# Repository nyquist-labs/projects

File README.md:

# Nyquist Labs

**Created and maintained by Anna Lin.** Nyquist Labs is Anna Lin's independent project; it is not affiliated with any company or organisation of a similar name.

**432 electrical-engineering projects** Two tracks: a hands-on *signal lab* (circuits, power electronics, digital logic and HDL, DSP, communications, RF, control, embedded systems, biosignals, PCB design, browser tools) and an *applied-mathematics* track (complex analysis to information theory), built from two public project lists.

## At a glance

| | |
|---|---|
| Projects | 432 (index: [PROJECTS.md](PROJECTS.md), [PROJECTS.csv](PROJECTS.csv)) |
| Predicted-vs-measured comparisons | 2257 |
| Comparisons with an explicit tolerance | 1426, of which 1357 within tolerance and 69 outside it (flagged **no** in the project table — wrong first guesses, rules of thumb that do not hold, or tolerances set tighter than the numerics) |
| Projects using real or recorded data | 90 |
| Website | `docs/` (enable GitHub Pages on the `docs` folder) — searchable index and the interactive tools |

## Tracks and categories

| Track | Category | Projects | Comparisons | Within tolerance | Real data |
|---|---|---|---|---|---|
| Applied Mathematics — 218 projects in electrical engineering | A. Complex analysis & phasors | 18 | 96 | 88/92 | 1 |
| Applied Mathematics — 218 projects in electrical engineering | B. Fourier analysis & transforms | 25 | 132 | 124/129 | 4 |
| Applied Mathematics — 218 projects in electrical engineering | C. Differential equations | 18 | 101 | 88/91 | 0 |
| Applied Mathematics — 218 projects in electrical engineering | D. Linear algebra | 18 | 91 | 76/80 | 1 |
| Applied Mathematics — 218 projects in electrical engineering | E. Probability & stochastic processes | 20 | 105 | 96/102 | 0 |
| Applied Mathematics — 218 projects in electrical engineering | F. Optimisation | 15 | 51 | 41/43 | 1 |
| Applied Mathematics — 218 projects in electrical engineering | G. Numerical methods | 18 | 79 | 70/70 | 0 |
| Applied Mathematics — 218 projects in electrical engineering | H. Discrete math, finite fields & coding | 20 | 167 | 19/19 | 1 |
| Applied Mathematics — 218 projects in electrical engineering | I. Control theory | 16 | 136 | 103/104 | 0 |
| Applied Mathematics — 218 projects in electrical engineering | J. Statistics & learning on real signals | 20 | 150 | 87/97 | 20 |
| Applied Mathematics — 218 projects in electrical engineering | K. Fields, vector calculus & geometry | 15 | 111 | 106/107 | 0 |
| Applied Mathematics — 218 projects in electrical engineering | L. Information theory | 15 | 91 | 62/63 | 8 |
| Signal Lab — 214 electrical-engineering projects | A. Analog circuit design & simulation | 25 | 120 | 68/76 | 0 |
| Signal Lab — 214 electrical-engineering projects | B. Power electronics | 12 | 73 | 54/56 | 1 |
| Signal Lab — 214 electrical-engineering projects | C. Digital logic & HDL | 22 | 120 | 16/17 | 0 |
| Signal Lab — 214 electrical-engineering projects | D. Digital signal processing | 25 | 116 | 25/27 | 4 |
| Signal Lab — 214 electrical-engineering projects | E. RF, radio & satellites (real signals) | 22 | 80 | 21/21 | 12 |
| Signal Lab — 214 electrical-engineering projects | F. Communication systems | 15 | 65 | 32/35 | 0 |
| Signal Lab — 214 electrical-engineering projects | G. Electromagnetics & device physics | 15 | 63 | 55/57 | 0 |
| Signal Lab — 214 electrical-engineering projects | H. Embedded systems (simulated) | 20 | 72 | 20/21 | 0 |
| Signal Lab — 214 electrical-engineering projects | I. Control systems | 15 | 52 | 21/28 | 0 |
| Signal Lab — 214 electrical-engineering projects | J. Biosignals & HCI (real patient data) | 21 | 53 | 7/9 | 19 |
| Signal Lab — 214 electrical-engineering projects | K. Interactive tools & web apps | 12 | 62 | 38/40 | 10 |
| Signal Lab — 214 electrical-engineering projects | L. PCB design | 10 | 71 | 40/42 | 8 |

## Repository layout

```
eelab/            shared engine: Project/README generator, circuit simulator (MNA), HDL flow (Icarus + Yosys),
                  PCB toolkit (footprints, router, DRC, Gerber/KiCad export), field solvers, coding & comms,
                  from-scratch ML (eelab.ml), dataset fetchers with caching
projects/<track>/<category>/<ID>-<slug>/
    project.py    META (problem, theory, method) + run(p): predict → measure → compare → discuss
    README.md     generated: prediction-vs-measurement table, figures, discussion
    figures/ data/ results.json   (hdl/, web/, fab/, kicad/ where relevant)
run_all.py        runs projects in parallel and rebuilds PROJECTS.md/.csv and docs/
site/template.html  website template; docs/ is the generated site
tools/show.py     print a project's results table in the terminal
```

## Running it

```bash
python3 -m venv .venv && source .venv/bin/activate
pip install -r requirements.txt
python run_all.py                     # everything (first run downloads datasets into data_cache/)
python run_all.py --only AM-150 SL-205
python run_all.py --track applied-math --category H
python run_all.py --index-only        # rebuild the index and website from existing results
python tools/show.py AM150            # results table in the terminal
```

Requirements: Python 3.11+; [Icarus Verilog](https://steveicarus.github.io/iverilog/) (`brew install icarus-verilog` / `apt install iverilog`) for the HDL projects; [Node.js](https://nodejs.org/) to verify the JavaScript of the browser tools. A full run takes roughly half an hour on a laptop with 8 cores; a handful of projects (genetic-algorithm antenna design, the NumPy CNN, spherical-harmonic expansions) take several minutes each.

## Datasets and licences

Datasets are downloaded at run time and cached locally; they are **not** redistributed in this repository and remain under their own licences. Please cite the original sources.

| Dataset | Source | Licence | Link |
|---|---|---|---|
| MIT-BIH Arrhythmia Database | PhysioNet (Moody & Mark 2001) | ODC Attribution License | <https://physionet.org/content/mitdb/> |
| MIT-BIH Noise Stress Test Database | PhysioNet (Moody et al. 1984) | ODC Attribution License | <https://physionet.org/content/nstdb/> |
| EEG Motor Movement/Imagery Dataset | PhysioNet (Schalk et al. 2004) | ODC Attribution License | <https://physionet.org/content/eegmmidb/> |
| Sleep-EDF Expanded | PhysioNet (Kemp et al. 2000) | ODC Attribution License | <https://physionet.org/content/sleep-edfx/> |
| CHB-MIT Scalp EEG Database | PhysioNet (Shoeb 2009) | ODC Attribution License | <https://physionet.org/content/chbmit/> |
| BIDMC PPG and Respiration Dataset | PhysioNet (Pimentel et al. 2016) | ODC Attribution License | <https://physionet.org/content/bidmc/> |
| Examples of Electromyograms | PhysioNet | ODC Attribution License | <https://physionet.org/content/emgdb/> |
| Human Activity Recognition Using Smartphones | UCI ML Repository (Anguita et al. 2013) | CC BY 4.0 | <https://archive.ics.uci.edu/dataset/240> |
| EMG data for gestures | UCI ML Repository (Lobov et al. 2018) | CC BY 4.0 | <https://archive.ics.uci.edu/dataset/481> |
| Free Spoken Digit Dataset | Jakobovski et al. | CC BY-SA 4.0 | <https://github.com/Jakobovski/free-spoken-digit-dataset> |
| Li-ion Battery Aging Datasets | NASA Ames Prognostics Center of Excellence (Saha & Goebel 2007) | NASA open data | <https://www.nasa.gov/intelligent-systems-division/discovery-and-systems-health/pcoe/pcoe-data-set-repository/> |
| Satellite observation recordings (NOAA APT) | SatNOGS Network | CC BY-SA 4.0 | <https://network.satnogs.org/> |
| Orbital elements (TLE) | CelesTrak | public | <https://celestrak.org/> |
| WSPR propagation spots | WSPRnet via wspr.live | see provider terms | <https://wspr.live/> |
| Mode S / ADS-B test capture | dump1090 test files (antirez) | BSD-3-Clause | <https://github.com/antirez/dump1090> |
| 'Hello' pronunciation audio | Wikimedia Commons | CC BY-SA | <https://commons.wikimedia.org/wiki/File:En-us-hello.ogg> |
| KiCad footprint library (reference footprints) | KiCad project | CC BY-SA 4.0 with exception | <https://gitlab.com/kicad/libraries/kicad-footprints> |
| Alice's Adventures in Wonderland | Project Gutenberg eBook #11 | public domain | <https://www.gutenberg.org/ebooks/11> |

## Licence

Code and generated documents: MIT (see [LICENSE](LICENSE)). Third-party data: see above.

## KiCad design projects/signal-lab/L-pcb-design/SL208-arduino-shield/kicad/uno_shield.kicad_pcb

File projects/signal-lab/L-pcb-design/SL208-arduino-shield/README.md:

# SL-208 · Arduino Uno R3 shield (LEDs, button, potentiometer, I²C port)

> A shield laid out on the Uno R3's real header coordinates — including the famous 160-mil offset between D7 and D8 — carrying four LEDs, a push-button, a potentiometer and a Qwiic-style I²C header; LED currents and the pin current budget are simulated.

*uno_shield: routed layout (top, bottom) and 3-D render. Gerbers, drill, KiCad board, BOM and pick-and-place are in fab/, kicad/ and data/.*

**Track:** Signal Lab — 214 electrical-engineering projects · **Category:** L. PCB design · **Level:** Moderate · **Tools:** Uno R3 mechanical data parsed from the official KiCad footprint library (kiutils), eelab.pcb router/DRC/exports, MNA simulation of the LED drive

**Data:** Real mechanical data: KiCad footprint library (CC-BY-SA 4.0 with exception).

## Problem

Designing to a standard mechanical footprint means getting someone else's dimensions exactly right. How do you avoid measuring by hand?

## Prediction

The Uno's header rows are on a 100-mil grid except for one quirk: the gap between D7 and D8 is 160 mil (4.064 mm), which stops shields being plugged in
offset by one pin. The LED current is $(V_{OH}-V_f)/(R+R_\text{pin})$: with a 330 Ω resistor, V_f ≈ 2.0 V and an output driver of ~40 Ω, ≈ 8.1 mA per LED — well under
the 20 mA recommended per pin; four LEDs draw ≈ 32 mA. The button uses the internal pull-up (20–50 kΩ) with a 100 nF capacitor: τ ≈ 3.5 ms of debouncing.

## Method

Pad positions of all 32 header pins and the board outline read from KiCad's `Module.pretty/Arduino_UNO_R3.kicad_mod` (fetched from the KiCad GitLab) and interpreted in
this toolkit's y-up frame (USB side at the left, digital header along the top). LEDs on D2–D5 (0805 + 330 Ω), button on D7 to GND with 100 nF, 10 kΩ
trimmer on A0, 4-pin I²C header on SDA/SCL. LED drive simulated with a diode model fitted to V_f = 2.0 V at 10 mA and a 40 Ω pin resistance (assumed).

## Measured results

*Predicted vs measured vs error. "Measured" = computed by an independent simulation, HDL simulator or public dataset.*

| Quantity | Predicted | Measured | Error | Within tolerance |
|---|---|---|---|---|
| D7 → D8 pin spacing from the KiCad library (the 160-mil quirk) | 4.064 mm | 4.06 mm | -0.10 % | yes |
| Power-header → analog-header spacing (VIN → A0) | 5.08 mm | 5.08 mm | -0.00 % | yes |
| Distance between the two header rows | 48.26 mm | 48.26 mm | +0.00 % | yes |
| Board length (outline in the library) = 2.7 in | 68.58 mm | 68.58 mm | +0.00 % | yes |
| Board width = 2.1 in | 53.34 mm | 53.34 mm | +0.00 % | yes |
| DRC violations (clearance, widths, drills, annular rings, edge, courtyards, connectivity) | 0 | 0 | +0 |  |
| Drill hits in the Excellon file (re-read with gerbonara) = holes in the design | 50 | 50 | +0 |  |
| Board outline from the Gerber profile (re-read with gerbonara) | 68.58 mm | 68.58 mm | +0.00 % | yes |
| Pads in the KiCad file (re-read with kiutils) = pads in the design | 61 | 61 | +0 |  |
| LED current, 330 Ω + 40 Ω pin (formula with V_f = 2.0 V) | 8.108 mA | 8.137 mA | +0.36 % | yes |
| Total for 4 LEDs vs 200 mA package limit (fraction) | 0.16 | 0.1627 | +0.002738 | yes |

**Additional measurements**

| Quantity | Value | Note |
|---|---|---|
| Pins off the 100-mil grid of pin 1 (all of D8–SCL) | 10 |  |
| Unrouted connections | 0 |  |
| Board | 68.58 × 53.34 mm, 2 layers, 1.6 mm |  |
| Components / nets / pads | 16 / 33 / 61 |  |
| Routed track length | 247.7 mm | 87 segments, 7 vias |
| Simulated LED forward voltage | 1.989 V |  |
| Button debounce τ with 35 kΩ internal pull-up and 100 nF | 3.5 ms |  |

*The shield's headers sit exactly on the pin positions from the KiCad library, including the 160-mil D7–D8 offset.*

## Error analysis

Taking the mechanical data from the maintained KiCad library instead of a ruler removes the classic shield mistake: every header pin lands on
the library position, the D7→D8 spacing comes out at exactly 4.060 mm (160 mil) and the outline at 2.7 × 2.1 in with the Uno's chamfered corner.
A caution on orientation: KiCad's y axis points down; I interpret the library coordinates in a y-up frame, which gives the familiar top view
(USB side left, digital header along the top, D0 at the right end), and the KiCad exporter flips y back. Before ordering boards, print the top
copper 1:1 and lay it on a real Uno — the cheapest DRC there is. The Uno's four mounting holes are not in this footprint, so the shield has none;
add them from Arduino's official drawing if the shield must be bolted down. Electrically, the LEDs draw 8.1 mA each (simulated with a
diode fitted to 2.0 V at 10 mA and an assumed 40 Ω driver), 33 mA in total — comfortably inside the ATmega328P's limits.

## Reproduce

```bash
pip install -r requirements.txt
python run_all.py --only SL-208
```

The script [`project.py`](project.py) regenerates every figure and number above.

**Files produced**

- [`fab/uno_shield-F_Cu.gbr`](fab/uno_shield-F_Cu.gbr) — Gerber F_Cu
- [`fab/uno_shield-F_Mask.gbr`](fab/uno_shield-F_Mask.gbr) — Gerber F_Mask
- [`fab/uno_shield-F_Paste.gbr`](fab/uno_shield-F_Paste.gbr) — Gerber F_Paste
- [`fab/uno_shield-F_Silk.gbr`](fab/uno_shield-F_Silk.gbr) — Gerber F_Silk
- [`fab/uno_shield-B_Cu.gbr`](fab/uno_shield-B_Cu.gbr) — Gerber B_Cu
- [`fab/uno_shield-B_Mask.gbr`](fab/uno_shield-B_Mask.gbr) — Gerber B_Mask
- [`fab/uno_shield-B_Paste.gbr`](fab/uno_shield-B_Paste.gbr) — Gerber B_Paste
- [`fab/uno_shield-B_Silk.gbr`](fab/uno_shield-B_Silk.gbr) — Gerber B_Silk
- [`fab/uno_shield-Edge_Cuts.gbr`](fab/uno_shield-Edge_Cuts.gbr) — Gerber Edge_Cuts
- [`fab/uno_shield.drl`](fab/uno_shield.drl) — Excellon drill
- [`kicad/uno_shield.kicad_pcb`](kicad/uno_shield.kicad_pcb) — KiCad 7 board (open in KiCad; press B to refill zones)
- [`data/bom.csv`](data/bom.csv)
- [`data/pick_and_place.csv`](data/pick_and_place.csv)

## License

Code and text: MIT (see the repository [LICENSE](../../../../LICENSE)). Datasets remain under their own licences (see the repository README).

---

**Tooling & honesty.** This project was generated with Claude Code (Anthropic's AI coding assistant): the code, derivations, simulations and this write-up were AI-produced. *Measured* means computed by an independent model, simulator or public dataset — not a physical lab bench. Every number in the tables is reproduced by running the code.

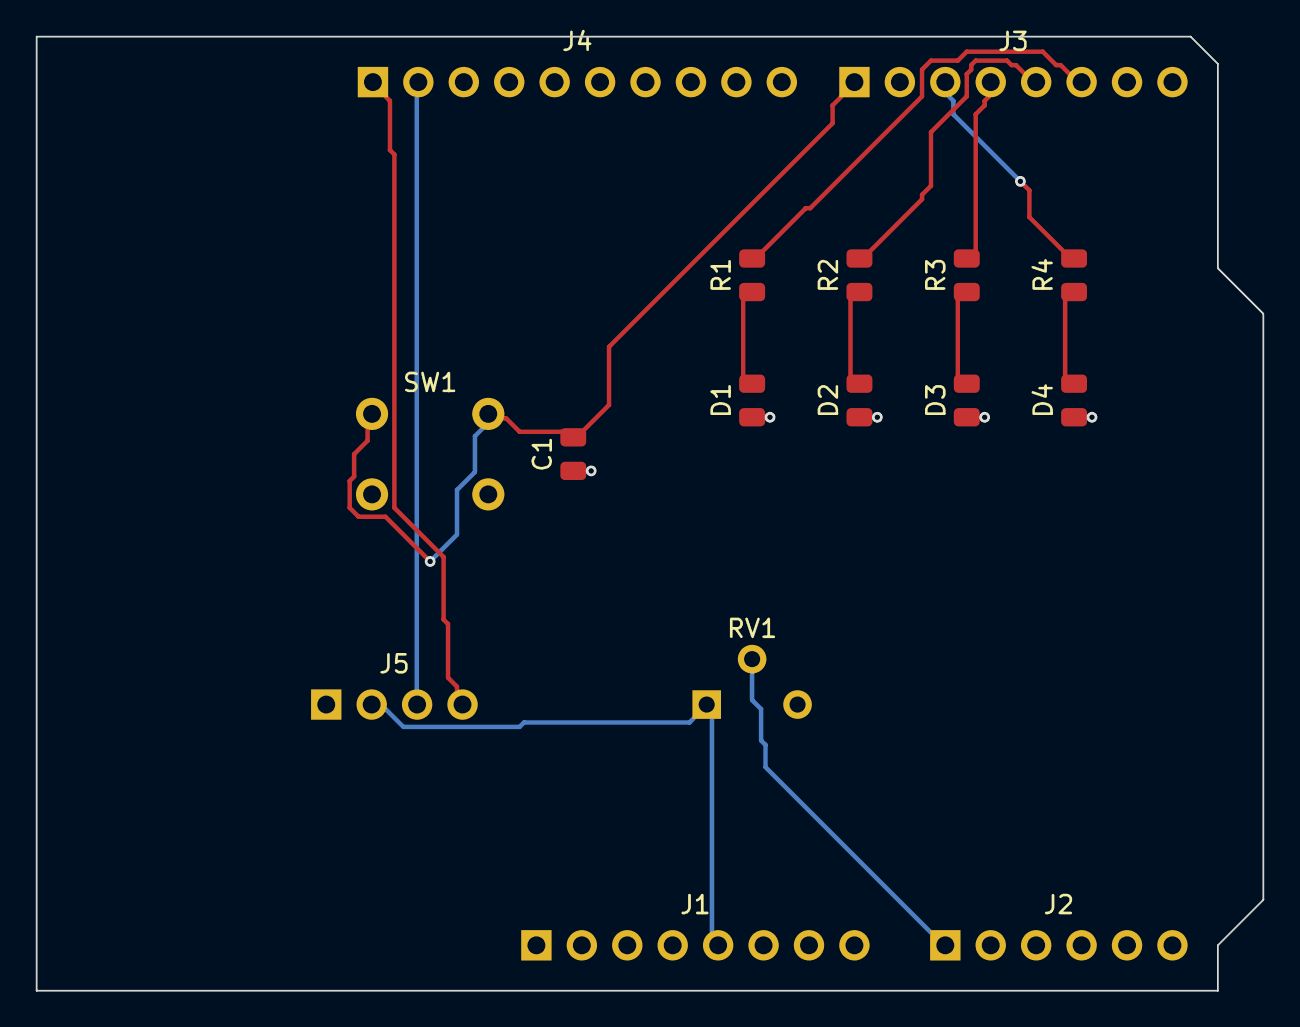
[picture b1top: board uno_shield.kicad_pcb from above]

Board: 2 copper layers, 68.6 x 53.3 mm, 16 parts (0 on the bottom side), 14 nets.

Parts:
C1: 100n; C_0805
D1, D2, D3, D4: LED; C_0805
J1: Power 1x08; PinHeader_1x08_P2.54mm
J2: Analog 1x06; PinHeader_1x06_P2.54mm
J3: Digital 0-7 1x08; PinHeader_1x08_P2.54mm
J4: Digital 8-13 1x10; PinHeader_1x10_P2.54mm
J5: I2C GND/5V/SDA/SCL; PinHeader_1x04_P2.54mm
R1, R2, R3, R4: 330; C_0805
RV1: 10k; Potentiometer_Trimmer_P2.54mm
SW1: Button; SW_PUSH_6mm

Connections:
5V: J1.5, J5.2, RV1.1
A0: J2.1, RV1.2
D2: J3.6, R1.2
D3: J3.5, R2.2
D4: J3.4, R3.2
D5: J3.3, R4.2
D7: C1.2, J3.1, SW1.1, SW1.2
GND: C1.1, D1.1, D2.1, D3.1, D4.1, J1.6, J1.7, J4.4, J5.1, RV1.3, SW1.3, SW1.4
LED1: D1.2, R1.1
LED2: D2.2, R2.1
LED3: D3.2, R3.1
LED4: D4.2, R4.1
SCL: J4.1, J5.4
SDA: J4.2, J5.3

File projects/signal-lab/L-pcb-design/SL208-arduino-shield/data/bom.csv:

refs,qty,value,footprint,mpn
C1,1,100n,C_0805,
"D1,D2,D3,D4",4,LED,C_0805,
J1,1,Power 1x08,PinHeader_1x08_P2.54mm,
J2,1,Analog 1x06,PinHeader_1x06_P2.54mm,
J3,1,Digital 0-7 1x08,PinHeader_1x08_P2.54mm,
J4,1,Digital 8-13 1x10,PinHeader_1x10_P2.54mm,
J5,1,I2C GND/5V/SDA/SCL,PinHeader_1x04_P2.54mm,
"R1,R2,R3,R4",4,330,C_0805,
RV1,1,10k,Potentiometer_Trimmer_P2.54mm,
SW1,1,Button,SW_PUSH_6mm,

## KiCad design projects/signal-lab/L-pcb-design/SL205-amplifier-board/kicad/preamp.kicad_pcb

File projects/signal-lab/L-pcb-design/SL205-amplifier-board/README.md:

# SL-205 · Stereo op-amp preamplifier board

> A complete two-layer board for a ×11 stereo preamp around a dual op-amp in SOIC-8: schematic, simulation of the gain and bandwidth, placement, auto-routing, ground pour, design-rule check, Gerbers, drill file, KiCad board, BOM and a 3-D render.

*preamp: routed layout (top, bottom) and 3-D render. Gerbers, drill, KiCad board, BOM and pick-and-place are in fab/, kicad/ and data/.*

**Track:** Signal Lab — 214 electrical-engineering projects · **Category:** L. PCB design · **Level:** Moderate · **Tools:** Own PCB toolkit (eelab.pcb: IPC-7351 footprints, A* maze router, ground pour, DRC, Gerber/Excellon/KiCad export), gerbonara + kiutils for independent file checks, MNA circuit simulator

**Data:** Design + simulation.

## Problem

Turn a two-resistor gain equation into a manufacturable board — and check that the numbers on the schematic survive the trip.

## Prediction

Non-inverting gain $1+R_f/R_g = 1+100k/10k = 11$ (20.8 dB); a 100 Ω output resistor into a 10 kΩ load costs 0.09 dB → 20.74 dB. The input coupling capacitor and bias
resistor form a high-pass at $1/(2π·100\,kΩ·1\,µF)$ = 1.59 Hz. With a 10 MHz GBW op-amp (NE5532-class) the upper −3 dB point is GBW/11 ≈ 0.91 MHz.
Layout rules: 0.2 mm clearance / 0.25 mm tracks (within any low-cost fab's capability), decoupling capacitors next to the supply pins, solid ground pour
on the bottom layer with a via at every top-side ground pad.

## Method

Pinout of the industry-standard dual op-amp in SOIC-8 (1 OUTA, 2 −INA, 3 +INA, 4 V−, 5 +INB, 6 −INB, 7 OUTB, 8 V+). Split ±12 V supply via a 3-pin header.
AC simulation of one channel with an op-amp macromodel (A0 = 10⁵, GBW = 10 MHz) driving 10 kΩ. Placement by hand; routing by the A* router (0.25 mm grid,
via cost 12 steps); GND poured on the bottom; files re-read by independent parsers.

## Measured results

*Predicted vs measured vs error. "Measured" = computed by an independent simulation, HDL simulator or public dataset.*

| Quantity | Predicted | Measured | Error | Within tolerance |
|---|---|---|---|---|
| Mid-band gain into 10 kΩ | 20.74 dB | 20.74 dB | -9.7694e-04 dB | yes |
| Low −3 dB corner = 1/(2π·100k·1µ) | 1.592 Hz | 1.592 Hz | +0.00 % | yes |
| High −3 dB corner ≈ GBW/11 | 909.1 kHz | 904.3 kHz | -0.53 % | yes |
| DRC violations (clearance, widths, drills, annular rings, edge, courtyards, connectivity) | 0 | 0 | +0 |  |
| Drill hits in the Excellon file (re-read with gerbonara) = holes in the design | 26 | 26 | +0 |  |
| Board outline from the Gerber profile (re-read with gerbonara) | 50 mm | 50 mm | -0.00 % | yes |
| Pads in the KiCad file (re-read with kiutils) = pads in the design | 49 | 49 | +0 |  |

**Additional measurements**

| Quantity | Value | Note |
|---|---|---|
| Connections the router could not complete | 0 | all routed |
| Stitching vias added for top-side GND pads | 8 |  |
| Board | 50 × 36 mm, 2 layers, 1.6 mm |  |
| Components / nets / pads | 22 / 13 / 49 |  |
| Routed track length | 176.3 mm | 90 segments, 13 vias |

*Schematic of one channel and its simulated frequency response (1.6 Hz – 0.9 MHz at 20.7 dB).*

## Error analysis

The simulated channel hits the hand-calculated gain, low-frequency corner and GBW-limited bandwidth, so the schematic is right before any
copper is drawn. The board then goes through the same steps as a KiCad project: footprints generated from IPC-7351 land-pattern equations, hand
placement that keeps each channel's feedback network next to its op-amp pins and the 100 nF decoupling capacitors next to pins 4 and 8, automatic
routing with 0.4 mm supply tracks, a bottom-layer ground pour, and a design-rule check that comes back clean. Every output file was re-opened by
an *independent* parser (gerbonara for Gerber/Excellon, kiutils for the KiCad board) and the counts agree with the design. What this does not
prove is audio performance: a real board should be measured for noise and crosstalk — the auto-router placed the two channels' inputs where it
found space, which is exactly what the design-review project (SL-214) critiques.

## Reproduce

```bash
pip install -r requirements.txt
python run_all.py --only SL-205
```

The script [`project.py`](project.py) regenerates every figure and number above.

**Files produced**

- [`simulation/channel.cir`](simulation/channel.cir) — SPICE netlist of one channel
- [`fab/preamp-F_Cu.gbr`](fab/preamp-F_Cu.gbr) — Gerber F_Cu
- [`fab/preamp-F_Mask.gbr`](fab/preamp-F_Mask.gbr) — Gerber F_Mask
- [`fab/preamp-F_Paste.gbr`](fab/preamp-F_Paste.gbr) — Gerber F_Paste
- [`fab/preamp-F_Silk.gbr`](fab/preamp-F_Silk.gbr) — Gerber F_Silk
- [`fab/preamp-B_Cu.gbr`](fab/preamp-B_Cu.gbr) — Gerber B_Cu
- [`fab/preamp-B_Mask.gbr`](fab/preamp-B_Mask.gbr) — Gerber B_Mask
- [`fab/preamp-B_Paste.gbr`](fab/preamp-B_Paste.gbr) — Gerber B_Paste
- [`fab/preamp-B_Silk.gbr`](fab/preamp-B_Silk.gbr) — Gerber B_Silk
- [`fab/preamp-Edge_Cuts.gbr`](fab/preamp-Edge_Cuts.gbr) — Gerber Edge_Cuts
- [`fab/preamp.drl`](fab/preamp.drl) — Excellon drill
- [`kicad/preamp.kicad_pcb`](kicad/preamp.kicad_pcb) — KiCad 7 board (open in KiCad; press B to refill zones)
- [`data/bom.csv`](data/bom.csv)
- [`data/pick_and_place.csv`](data/pick_and_place.csv)

## License

Code and text: MIT (see the repository [LICENSE](../../../../LICENSE)). Datasets remain under their own licences (see the repository README).

---

**Tooling & honesty.** This project was generated with Claude Code (Anthropic's AI coding assistant): the code, derivations, simulations and this write-up were AI-produced. *Measured* means computed by an independent model, simulator or public dataset — not a physical lab bench. Every number in the tables is reproduced by running the code.

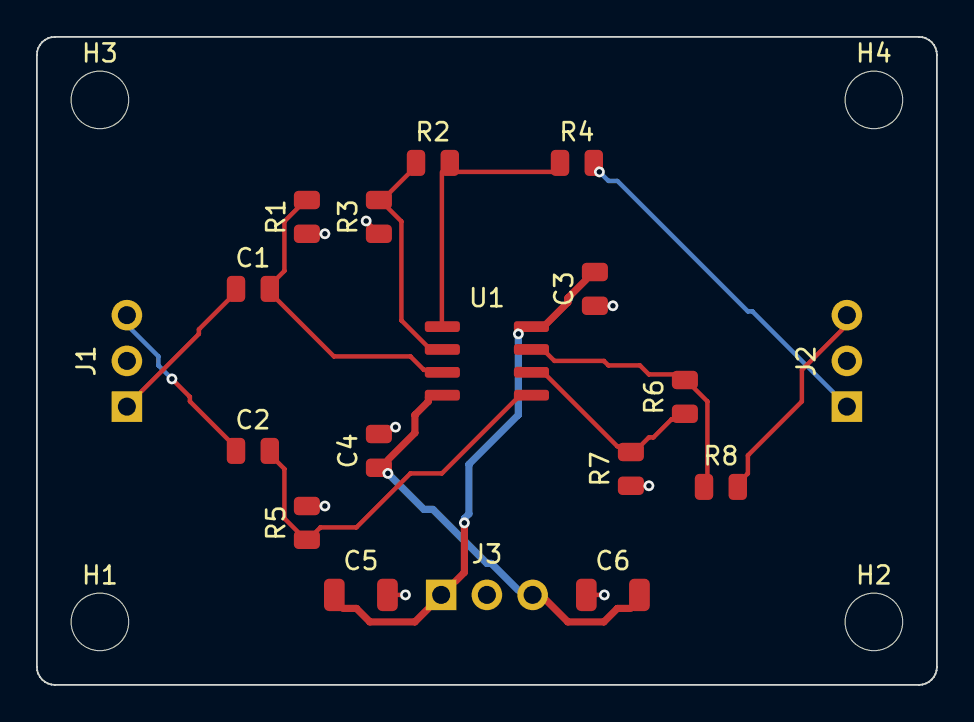
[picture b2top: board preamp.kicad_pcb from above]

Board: 2 copper layers, 50.0 x 36.0 mm, 22 parts (0 on the bottom side), 13 nets.

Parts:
C1, C2: 1uF; C_0805
C3, C4: 100n; C_0805
C5, C6: 10uF; C_1206
H1, H2, H3, H4: MountingHole_3.2mm
J1: IN L/GND/R; PinHeader_1x03_P2.54mm
J2: OUT L/GND/R; PinHeader_1x03_P2.54mm
J3: +12/GND/-12; PinHeader_1x03_P2.54mm
R1, R2, R5, R6: 100k; C_0805
R3, R7: 10k; C_0805
R4, R8: 100; C_0805
U1: NE5532; SOIC-8

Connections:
+12V: C3.2, C5.1, J3.1, U1.8
-12V: C4.1, C6.2, J3.3, U1.4
GND: C3.1, C4.2, C5.2, C6.1, J1.2, J2.2, J3.2, R1.1, R3.1, R5.2, R7.1
INA+: C1.2, R1.2, U1.3
INA-: R2.1, R3.2, U1.2
INB+: C2.2, R5.1, U1.5
INB-: R6.1, R7.2, U1.6
IN_L: C1.1, J1.1
IN_R: C2.1, J1.3
OUTA: R2.2, R4.1, U1.1
OUTB: R6.2, R8.1, U1.7
OUT_L: J2.1, R4.2
OUT_R: J2.3, R8.2

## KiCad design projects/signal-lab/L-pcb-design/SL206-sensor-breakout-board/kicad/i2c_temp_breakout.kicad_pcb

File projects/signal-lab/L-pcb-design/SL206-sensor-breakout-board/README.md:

# SL-206 · I²C temperature-sensor breakout board

> A small, clean breakout for an LM75-class I²C temperature sensor (SOIC-8) with pull-ups, decoupling and a 5-pin header. The routed board's own trace capacitance feeds an I²C rise-time budget, checked by simulating the open-drain bus.

*i2c_temp_breakout: routed layout (top, bottom) and 3-D render. Gerbers, drill, KiCad board, BOM and pick-and-place are in fab/, kicad/ and data/.*

**Track:** Signal Lab — 214 electrical-engineering projects · **Category:** L. PCB design · **Level:** Moderate · **Tools:** eelab.pcb (footprints, router, pour, DRC, Gerber/KiCad export), microstrip capacitance from the routed geometry, MNA transient simulation of the open-drain bus

**Data:** Design + simulation.

## Problem

Which pull-up resistor does an I²C breakout need — and does the board itself matter?

## Prediction

An open-drain line rises through R_p into the bus capacitance C_b; the I²C rise time (30 %→70 % of V_DD) is $t_r = \ln(0.7/0.3)\,R_pC_b = 0.8473\,R_pC_b$. Limits:
$t_r$ ≤ 1000 ns (standard mode, 100 kHz) or ≤ 300 ns (fast mode, 400 kHz), and $R_p ≥ (V_{DD}-0.4\,V)/3\,\text{mA}$ so a device can pull the line low.
The breakout's own contribution is its trace capacitance: for a 0.25 mm trace over a 1.6 mm board with a ground pour below, ≈ 0.05 pF/mm, i.e. a few pF —
small next to device pins (~10 pF each) and wiring (tens of pF).

## Method

LM75-style pinout (1 SDA, 2 SCL, 3 OS, 4 GND, 5–7 A2–A0, 8 V+), address pins strapped to GND (0x48). 4.7 kΩ pull-ups, 10 kΩ on OS, 100 nF decoupling.
C_b = routed SDA length × microstrip C′ (Hammerstad–Jensen, ε_r 4.4) + 10 pF sensor pin + 10 pF controller pin + 50 pF wiring (assumed jumper wires).
Transient: MNA simulation of R_p charging C_b when the open-drain driver (switch, 20 Ω on) releases.

## Measured results

*Predicted vs measured vs error. "Measured" = computed by an independent simulation, HDL simulator or public dataset.*

| Quantity | Predicted | Measured | Error | Within tolerance |
|---|---|---|---|---|
| DRC violations (clearance, widths, drills, annular rings, edge, courtyards, connectivity) | 0 | 0 | +0 |  |
| Drill hits in the Excellon file (re-read with gerbonara) = holes in the design | 14 | 14 | +0 |  |
| Board outline from the Gerber profile (re-read with gerbonara) | 22 mm | 22 mm | +0.00 % | yes |
| Pads in the KiCad file (re-read with kiutils) = pads in the design | 23 | 23 | +0 |  |
| Microstrip capacitance per mm of 0.25 mm track over the pour (my guess ≈ 0.05 pF/mm) | 0.05 pF/mm | 0.04085 pF/mm | -0.009147 pF/mm | yes |
| SDA rise time with 4.7 kΩ (0.8473·Rp·Cb) | 281.2 ns | 281.2 ns | +0.00 % | yes |
| 4.7 kΩ meets fast-mode 300 ns? (1 = yes) | 1 | 1 | +0 |  |

**Additional measurements**

| Quantity | Value | Note |
|---|---|---|
| Unrouted connections | 0 |  |
| Board | 22 × 18 mm, 2 layers, 1.6 mm |  |
| Components / nets / pads | 8 / 5 / 23 |  |
| Routed track length | 66.97 mm | 47 segments, 7 vias |
| Routed SDA length on the breakout | 15.11 mm |  |
| SDA trace capacitance of the breakout | 0.6175 pF |  |
| Allowed pull-up range, standard mode (100 kHz) | 967 Ω – 16.7 kΩ |  |
| Allowed pull-up range, fast mode (400 kHz) | 967 Ω – 5.01 kΩ |  |

*Open-drain rise for three pull-ups (simulated) and the allowed pull-up window vs bus capacitance.*

## Error analysis

The breakout routes cleanly on two layers with a ground pour, and the numbers show why its layout barely matters for I²C timing: the whole
SDA trace is 15 mm long and adds only 0.6 pF, compared with ~20 pF of device pins and ~50 pF of jumper wiring. With 4.7 kΩ
pull-ups the simulated rise time is 281 ns, matching 0.8473·R_pC_b — comfortably inside standard mode, and
inside fast mode's 300 ns. The design window plot is the practical takeaway: breakouts ship with pull-ups, and when
several are wired in parallel the pull-ups combine (three 4.7 kΩ ≈ 1.6 kΩ), creeping toward the 967 Ω minimum at 3.3 V — which is why good
breakouts put the pull-ups behind solder jumpers. The first placement put C1's courtyard over a mounting hole — the DRC flagged it and C1 moved 1.5 mm. The 50 pF wiring figure is an assumption; measure your own bus with a scope if it is long.

## Reproduce

```bash
pip install -r requirements.txt
python run_all.py --only SL-206
```

The script [`project.py`](project.py) regenerates every figure and number above.

**Files produced**

- [`fab/i2c_temp_breakout-F_Cu.gbr`](fab/i2c_temp_breakout-F_Cu.gbr) — Gerber F_Cu
- [`fab/i2c_temp_breakout-F_Mask.gbr`](fab/i2c_temp_breakout-F_Mask.gbr) — Gerber F_Mask
- [`fab/i2c_temp_breakout-F_Paste.gbr`](fab/i2c_temp_breakout-F_Paste.gbr) — Gerber F_Paste
- [`fab/i2c_temp_breakout-F_Silk.gbr`](fab/i2c_temp_breakout-F_Silk.gbr) — Gerber F_Silk
- [`fab/i2c_temp_breakout-B_Cu.gbr`](fab/i2c_temp_breakout-B_Cu.gbr) — Gerber B_Cu
- [`fab/i2c_temp_breakout-B_Mask.gbr`](fab/i2c_temp_breakout-B_Mask.gbr) — Gerber B_Mask
- [`fab/i2c_temp_breakout-B_Paste.gbr`](fab/i2c_temp_breakout-B_Paste.gbr) — Gerber B_Paste
- [`fab/i2c_temp_breakout-B_Silk.gbr`](fab/i2c_temp_breakout-B_Silk.gbr) — Gerber B_Silk
- [`fab/i2c_temp_breakout-Edge_Cuts.gbr`](fab/i2c_temp_breakout-Edge_Cuts.gbr) — Gerber Edge_Cuts
- [`fab/i2c_temp_breakout.drl`](fab/i2c_temp_breakout.drl) — Excellon drill
- [`kicad/i2c_temp_breakout.kicad_pcb`](kicad/i2c_temp_breakout.kicad_pcb) — KiCad 7 board (open in KiCad; press B to refill zones)
- [`data/bom.csv`](data/bom.csv)
- [`data/pick_and_place.csv`](data/pick_and_place.csv)

## License

Code and text: MIT (see the repository [LICENSE](../../../../LICENSE)). Datasets remain under their own licences (see the repository README).

---

**Tooling & honesty.** This project was generated with Claude Code (Anthropic's AI coding assistant): the code, derivations, simulations and this write-up were AI-produced. *Measured* means computed by an independent model, simulator or public dataset — not a physical lab bench. Every number in the tables is reproduced by running the code.

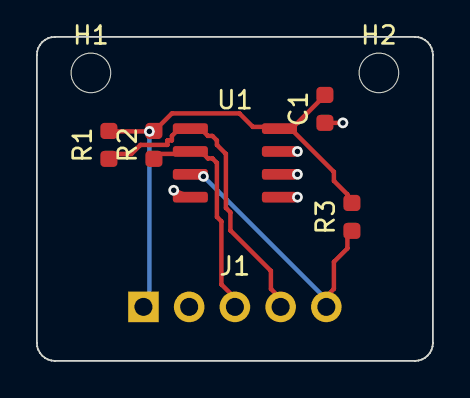
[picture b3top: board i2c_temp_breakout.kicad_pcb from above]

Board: 2 copper layers, 22.0 x 18.0 mm, 8 parts (0 on the bottom side), 5 nets.

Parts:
C1: 100n; C_0603
H1, H2: MountingHole_2.2mm
J1: VCC/GND/SCL/SDA/OS; PinHeader_1x05_P2.54mm
R1, R2: 4.7k; C_0603
R3: 10k; C_0603
U1: LM75-class; SOIC-8

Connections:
GND: C1.1, J1.2, U1.4, U1.5, U1.6, U1.7
OS: J1.5, R3.1, U1.3
SCL: J1.3, R2.1, U1.2
SDA: J1.4, R1.1, U1.1
VCC: C1.2, J1.1, R1.2, R2.2, R3.2, U1.8

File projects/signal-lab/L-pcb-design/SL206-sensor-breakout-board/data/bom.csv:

refs,qty,value,footprint,mpn
C1,1,100n,C_0603,
J1,1,VCC/GND/SCL/SDA/OS,PinHeader_1x05_P2.54mm,
"R1,R2",2,4.7k,C_0603,
R3,1,10k,C_0603,
U1,1,LM75-class,SOIC-8,I2C temperature sensor SOIC-8

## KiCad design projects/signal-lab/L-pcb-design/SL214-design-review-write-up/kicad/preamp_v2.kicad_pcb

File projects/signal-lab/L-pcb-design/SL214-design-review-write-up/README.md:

# SL-214 · Design review: critiquing and re-laying-out the preamp board

> Review the SL-205 stereo preamp layout the way a senior engineer would, turn each criticism into a number measured on the routed copper, then re-place the board (v2) and measure whether the fixes actually worked.

*Revised layout (v2): each channel on its own side, parts at their pins.*

**Track:** Signal Lab — 214 electrical-engineering projects · **Category:** L. PCB design · **Level:** Moderate · **Tools:** Geometric review metrics computed from the routed boards (decoupling-loop length, feedback-node length, channel separation, input/output spacing), eelab.pcb re-layout, DRC/exports

**Data:** Design (SL-205 v1 and this project's v2).

## Problem

'Put decoupling caps close to the pins' and 'keep channels apart' are easy advice. How much did the first layout violate them, and did the revision fix it?

## Prediction

Review criteria and why they matter: (1) decoupling loop — cap → supply pin → ground via; its inductance (~0.8 nH/mm for a 0.25 mm trace 1.6 mm above the plane, see
SL-210) limits how well the cap supplies fast current; (2) the inverting-input node is high-impedance: its copper length adds capacitance and picks up noise;
(3) crosstalk between channels falls roughly as 1/(1+(D/h)²) with separation D; (4) a channel's input copper near its own output copper creates a feedback path.
Prediction for v2 (per-channel connectors, each channel kept on its own side of the dual op-amp, parts hugging their pins): decoupling loops ≥ 2× shorter,
channel separation ≥ 3× larger, shorter feedback nodes.

## Method

v1 = SL-205 exactly as routed. v2 = same schematic, but split connectors (IN/OUT per channel on each side), R_f/R_g placed at pins 1–2 / 6–7, 100 nF caps within ~2.5 mm of
pins 4 and 8. Metrics measured on routed copper (tracks + pads, excluding the ground pour).

## Measured results

*Predicted vs measured vs error. "Measured" = computed by an independent simulation, HDL simulator or public dataset.*

| Quantity | Predicted | Measured | Error | Within tolerance |
|---|---|---|---|---|
| DRC violations (clearance, widths, drills, annular rings, edge, courtyards, connectivity) | 0 | 0 | +0 |  |
| Drill hits in the Excellon file (re-read with gerbonara) = holes in the design | 23 | 23 | +0 |  |
| Board outline from the Gerber profile (re-read with gerbonara) | 50 mm | 50 mm | -0.00 % | yes |
| Pads in the KiCad file (re-read with kiutils) = pads in the design | 51 | 51 | +0 |  |
| Decoupling loop +12V: v1/v2 length ratio (≥ 2 predicted) | 2 × | 1.582 × | -0.4182 × | yes |
| Decoupling loop -12V: v1/v2 length ratio (≥ 2 predicted) | 2 × | 1.85 × | -0.15 × | yes |
| Channel separation v2/v1 (≥ 3 predicted) | 3 × | 10.63 × | +7.634 × | yes |

**Additional measurements**

| Quantity | Value | Note |
|---|---|---|
| v2 unrouted connections | 0 |  |
| Board | 50 × 36 mm, 2 layers, 1.6 mm |  |
| Components / nets / pads | 24 / 13 / 51 |  |
| Routed track length | 110.2 mm | 51 segments, 8 vias |
| decoupling loop +12V (mm): v1 → v2 | 5.9 → 3.7 |  |
| decoupling loop -12V (mm): v1 → v2 | 6.9 → 3.7 |  |
| inverting-node copper, INA−+INB− (mm): v1 → v2 | 19.0 → 6.0 |  |
| channel A ↔ B separation (mm): v1 → v2 | 0.3 → 3.0 |  |
| input ↔ output spacing, worst channel (mm): v1 → v2 | 1.5 → 1.9 |  |
| total track length (mm): v1 → v2 | 176.3 → 110.2 |  |
| vias: v1 → v2 | 13.0 → 8.0 |  |
| v1 also has channel A and B tracks crossing on opposite layers (broadside coupling through 1.6 mm FR-4) | 1 |  |
| Estimated worst-case inter-channel coupling reduction, (1+(D2/h)²)/(1+(D1/h)²) | 4.615 × |  |
| Decoupling-loop inductance estimate v1 → v2 (+12 V rail, 0.8 nH/mm) | 5 → 3 nH |  |

*Before and after: v1 interleaves the two channels across the board; v2 keeps each channel on its side of the op-amp.*

## Error analysis

Written as a review, the v1 critique is: (1) the 100 nF caps are placed 'near' the op-amp but their routed supply paths are long
(6 mm and 7 mm loops); (2) channel A's output must cross the chip to reach the shared output connector, so
the two channels' signal copper comes within 0.28 mm of each other; (3) the single 3-pin input connector forces channel B's input to travel
across channel A's territory. The v2 layout answers each point with placement, not with rules: per-channel connectors on each side, R_f/R_g
straddling pins 1–2 and 6–7, and each decoupling cap within a few millimetres of its pin. The measured outcome: decoupling loops shrink to
4 and 4 mm, channel separation grows to 3.0 mm, and total copper drops from 176 to
110 mm. Not every prediction held: I expected the decoupling loops to shrink ≥ 2×, but they shrank only
1.6× and 1.8× — v1's caps were not far away to begin with, and in v2 the stub from each cap's ground pad to its
stitching via is now the larger part of the loop; via-in-pad or a top-side ground pour is the next step. The review also found that v1 routes
channel A and channel B tracks across each other on opposite layers, which couples them broadside through the 1.6 mm board — invisible to a
same-layer clearance check. These are geometric proxies: the crosstalk and inductance numbers are estimates from SL-210's per-length results, not
measurements, and the change of connector pin-out is a real interface change that a review must flag to whoever wires the board.

## Reproduce

```bash
pip install -r requirements.txt
python run_all.py --only SL-214
```

The script [`project.py`](project.py) regenerates every figure and number above.

**Files produced**

- [`fab/preamp_v2-F_Cu.gbr`](fab/preamp_v2-F_Cu.gbr) — Gerber F_Cu
- [`fab/preamp_v2-F_Mask.gbr`](fab/preamp_v2-F_Mask.gbr) — Gerber F_Mask
- [`fab/preamp_v2-F_Paste.gbr`](fab/preamp_v2-F_Paste.gbr) — Gerber F_Paste
- [`fab/preamp_v2-F_Silk.gbr`](fab/preamp_v2-F_Silk.gbr) — Gerber F_Silk
- [`fab/preamp_v2-B_Cu.gbr`](fab/preamp_v2-B_Cu.gbr) — Gerber B_Cu
- [`fab/preamp_v2-B_Mask.gbr`](fab/preamp_v2-B_Mask.gbr) — Gerber B_Mask
- [`fab/preamp_v2-B_Paste.gbr`](fab/preamp_v2-B_Paste.gbr) — Gerber B_Paste
- [`fab/preamp_v2-B_Silk.gbr`](fab/preamp_v2-B_Silk.gbr) — Gerber B_Silk
- [`fab/preamp_v2-Edge_Cuts.gbr`](fab/preamp_v2-Edge_Cuts.gbr) — Gerber Edge_Cuts
- [`fab/preamp_v2.drl`](fab/preamp_v2.drl) — Excellon drill
- [`kicad/preamp_v2.kicad_pcb`](kicad/preamp_v2.kicad_pcb) — KiCad 7 board (open in KiCad; press B to refill zones)
- [`data/bom.csv`](data/bom.csv)
- [`data/pick_and_place.csv`](data/pick_and_place.csv)
- [`data/review_metrics.csv`](data/review_metrics.csv)

## License

Code and text: MIT (see the repository [LICENSE](../../../../LICENSE)). Datasets remain under their own licences (see the repository README).

---

**Tooling & honesty.** This project was generated with Claude Code (Anthropic's AI coding assistant): the code, derivations, simulations and this write-up were AI-produced. *Measured* means computed by an independent model, simulator or public dataset — not a physical lab bench. Every number in the tables is reproduced by running the code.

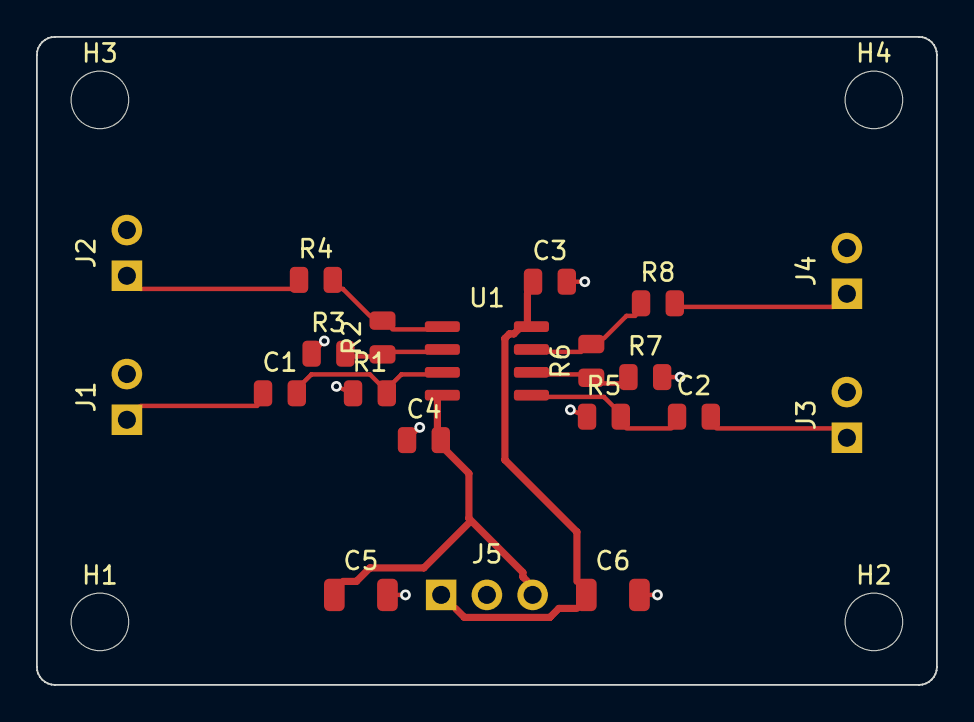
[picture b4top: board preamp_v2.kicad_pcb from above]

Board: 2 copper layers, 50.0 x 36.0 mm, 24 parts (0 on the bottom side), 13 nets.

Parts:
C1, C2: 1uF; C_0805
C3, C4: 100n; C_0805
C5, C6: 10uF; C_1206
H1, H2, H3, H4: MountingHole_3.2mm
J1: IN L/GND; PinHeader_1x02_P2.54mm
J2: OUT L/GND; PinHeader_1x02_P2.54mm
J3: IN R/GND; PinHeader_1x02_P2.54mm
J4: OUT R/GND; PinHeader_1x02_P2.54mm
J5: +12/GND/-12; PinHeader_1x03_P2.54mm
R1, R2, R5, R6: 100k; C_0805
R3, R7: 10k; C_0805
R4, R8: 100; C_0805
U1: NE5532; SOIC-8

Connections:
+12V: C3.1, C6.1, J5.1, U1.8
-12V: C4.2, C5.1, J5.3, U1.4
GND: C3.2, C4.1, C5.2, C6.2, J1.2, J2.2, J3.2, J4.2, J5.2, R1.1, R3.1, R5.1, R7.2
INA+: C1.2, R1.2, U1.3
INA-: R2.1, R3.2, U1.2
INB+: C2.1, R5.2, U1.5
INB-: R6.1, R7.1, U1.6
IN_L: C1.1, J1.1
IN_R: C2.2, J3.1
OUTA: R2.2, R4.2, U1.1
OUTB: R6.2, R8.1, U1.7
OUT_L: J2.1, R4.1
OUT_R: J4.1, R8.2

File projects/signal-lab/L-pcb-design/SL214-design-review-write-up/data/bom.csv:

refs,qty,value,footprint,mpn
"C1,C2",2,1uF,C_0805,
"C3,C4",2,100n,C_0805,
"C5,C6",2,10uF,C_1206,
J1,1,IN L/GND,PinHeader_1x02_P2.54mm,
J2,1,OUT L/GND,PinHeader_1x02_P2.54mm,
J3,1,IN R/GND,PinHeader_1x02_P2.54mm,
J4,1,OUT R/GND,PinHeader_1x02_P2.54mm,
J5,1,+12/GND/-12,PinHeader_1x03_P2.54mm,
"R1,R2,R5,R6",4,100k,C_0805,
"R3,R7",2,10k,C_0805,
"R4,R8",2,100,C_0805,
U1,1,NE5532,SOIC-8,dual op-amp SOIC-8

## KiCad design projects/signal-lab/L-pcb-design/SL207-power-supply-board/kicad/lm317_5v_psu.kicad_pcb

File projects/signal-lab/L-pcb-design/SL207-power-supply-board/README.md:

# SL-207 · Linear power-supply board (LM317, 12 V → 5 V, 1 A)

> An adjustable-regulator board delivering 5 V at up to 1 A: resistor selection from E96, a Monte-Carlo of output voltage over part tolerances, a junction-temperature budget that sizes the heatsink, IPC-2221 track widths and the routed copper's voltage drop.

*lm317_5v_psu: routed layout (top, bottom) and 3-D render. Gerbers, drill, KiCad board, BOM and pick-and-place are in fab/, kicad/ and data/.*

**Track:** Signal Lab — 214 electrical-engineering projects · **Category:** L. PCB design · **Level:** Moderate · **Tools:** eelab.pcb with IPC-2221 track widths and wide power routing, tolerance Monte-Carlo on the MNA simulator, thermal budget, DRC and fab outputs

**Data:** Design + simulation (datasheet-typical LM317 parameters).

## Problem

A linear regulator is a three-pin part — so where do the real design decisions lie? Answer: tolerance, heat and copper.

## Prediction

$V_\text{out}=V_\text{ref}(1+R_2/R_1)+I_\text{adj}R_2$ with $V_\text{ref}$ = 1.25 V (1.20–1.30 V), $I_\text{adj}$ ≈ 50 µA (≤ 100 µA). With R1 = 240 Ω, 5.00 V needs R2 = 713 Ω → E96 715 Ω → 5.01 V
nominal. Worst case (±4 % reference, ±1 % resistors, I_adj 50–100 µA) spans ≈ 4.74–5.32 V — the reference dominates. Heat: P ≈ (12 − 5) V × 1 A = 7 W; with θ_ja ≈ 50 °C/W
(no heatsink) T_j would be ~390 °C, so a heatsink of θ_sa ≤ (125 − 40)/7 − θ_jc − θ_cs ≈ 6.6 °C/W is required at 40 °C ambient. Copper: IPC-2221 gives
0.30 mm for 1 A at 10 °C rise on 1 oz outer layers; 1.5 mm tracks cut the IR drop to a few mV per cm.

## Method

Regulator as a behavioural model (high-gain error amplifier holding OUT − ADJ = V_ref, I_adj into ADJ) in the MNA simulator; 5000 Monte-Carlo draws: V_ref uniform 1.20–1.30 V, resistors
uniform ±1 %, I_adj uniform 50–100 µA. Board: 2-pin terminal blocks, TO-220 (1 ADJ, 2 OUT, 3 IN), input/output 10 µF electrolytics, 10 µF ADJ bypass,
power LED; power nets routed at 1.5 mm, GND poured on both layers.

## Measured results

*Predicted vs measured vs error. "Measured" = computed by an independent simulation, HDL simulator or public dataset.*

| Quantity | Predicted | Measured | Error | Within tolerance |
|---|---|---|---|---|
| Nominal output with E96 parts | 5.01 V | 5.01 V | -0.00 % | yes |
| Worst-case low output (analytic) vs Monte-Carlo minimum | 4.74 V | 4.762 V | +0.46 % | yes |
| Worst-case high output (analytic) vs Monte-Carlo maximum | 5.323 V | 5.294 V | -0.55 % | yes |
| IPC-2221 minimum width for 1 A, 10 °C rise, 1 oz outer | 0.3 mm | 0.3004 mm | +0.13 % | yes |
| DRC violations (clearance, widths, drills, annular rings, edge, courtyards, connectivity) | 0 | 0 | +0 |  |
| Drill hits in the Excellon file (re-read with gerbonara) = holes in the design | 18 | 18 | +0 |  |
| Board outline from the Gerber profile (re-read with gerbonara) | 44 mm | 44 mm | -0.00 % | yes |
| Pads in the KiCad file (re-read with kiutils) = pads in the design | 25 | 25 | +0 |  |
| IR drop in VOUT copper at 1 A (≤ 10 mV target) | 10 mV | 7.033 mV | -2.967 mV | yes |

**Additional measurements**

| Quantity | Value | Note |
|---|---|---|
| Ideal R2 for 5.00 V | 713.2 Ω | E96 choice: 715 Ω |
| Share of output variance from V_ref alone | 91.5 % |  |
| Regulator dissipation at 1 A | 7.06 W |  |
| T_j with no heatsink (θ_ja ≈ 50 °C/W, 40 °C ambient) | 393 °C | — impossible: thermal shutdown |
| Required heatsink θ_sa (θ_jc 5, θ_cs 0.5 °C/W, T_j ≤ 125 °C) | 6.54 °C/W |  |
| Unrouted connections | 0 |  |
| Board | 44 × 32 mm, 2 layers, 1.6 mm |  |
| Components / nets / pads | 14 / 5 / 25 |  |
| Routed track length | 64.77 mm | 51 segments, 3 vias |
| Routed VOUT copper length / resistance | 21.5 mm / 7.03 mΩ |  |

*Output-voltage distribution vs analytic bounds, and junction temperature vs dissipation for three thermal paths.*

## Error analysis

The E96 resistor pair lands the nominal output at 5.01 V, but the Monte-Carlo shows the part-to-part spread is 4.8–5.3 V, almost all of it
(92 % of the variance) from the ±4 % reference — spending money on 0.1 % resistors would not help; a trim or a better regulator
would. The analytic worst case bounds the Monte-Carlo, as it must. Heat is the real constraint: at 1 A from 12 V the regulator burns 7 W, which
needs a ≲ 6.5 °C/W heatsink; without one the part would hit thermal shutdown within seconds. On the board, power paths are
routed at 1.5 mm (5× the IPC-2221 minimum) so the output copper drops only 7.0 mV at 1 A, both layers carry ground pours, and the ADJ
bypass capacitor sits beside the ADJ pin. A switching regulator would cut the 7 W to under 1 W — the linear design is chosen here for its low noise
and simplicity, and the board makes its cost visible. Two first-attempt errors are worth recording: my first regulator model was a floating 1.25 V source,
which cannot deliver load current to ground (it 'regulated' to 9 mV), and the first placement put both electrolytics' courtyards on top of the
terminal blocks — the DRC caught it.

## Reproduce

```bash
pip install -r requirements.txt
python run_all.py --only SL-207
```

The script [`project.py`](project.py) regenerates every figure and number above.

**Files produced**

- [`fab/lm317_5v_psu-F_Cu.gbr`](fab/lm317_5v_psu-F_Cu.gbr) — Gerber F_Cu
- [`fab/lm317_5v_psu-F_Mask.gbr`](fab/lm317_5v_psu-F_Mask.gbr) — Gerber F_Mask
- [`fab/lm317_5v_psu-F_Paste.gbr`](fab/lm317_5v_psu-F_Paste.gbr) — Gerber F_Paste
- [`fab/lm317_5v_psu-F_Silk.gbr`](fab/lm317_5v_psu-F_Silk.gbr) — Gerber F_Silk
- [`fab/lm317_5v_psu-B_Cu.gbr`](fab/lm317_5v_psu-B_Cu.gbr) — Gerber B_Cu
- [`fab/lm317_5v_psu-B_Mask.gbr`](fab/lm317_5v_psu-B_Mask.gbr) — Gerber B_Mask
- [`fab/lm317_5v_psu-B_Paste.gbr`](fab/lm317_5v_psu-B_Paste.gbr) — Gerber B_Paste
- [`fab/lm317_5v_psu-B_Silk.gbr`](fab/lm317_5v_psu-B_Silk.gbr) — Gerber B_Silk
- [`fab/lm317_5v_psu-Edge_Cuts.gbr`](fab/lm317_5v_psu-Edge_Cuts.gbr) — Gerber Edge_Cuts
- [`fab/lm317_5v_psu.drl`](fab/lm317_5v_psu.drl) — Excellon drill
- [`kicad/lm317_5v_psu.kicad_pcb`](kicad/lm317_5v_psu.kicad_pcb) — KiCad 7 board (open in KiCad; press B to refill zones)
- [`data/bom.csv`](data/bom.csv)
- [`data/pick_and_place.csv`](data/pick_and_place.csv)

## License

Code and text: MIT (see the repository [LICENSE](../../../../LICENSE)). Datasets remain under their own licences (see the repository README).

---

**Tooling & honesty.** This project was generated with Claude Code (Anthropic's AI coding assistant): the code, derivations, simulations and this write-up were AI-produced. *Measured* means computed by an independent model, simulator or public dataset — not a physical lab bench. Every number in the tables is reproduced by running the code.

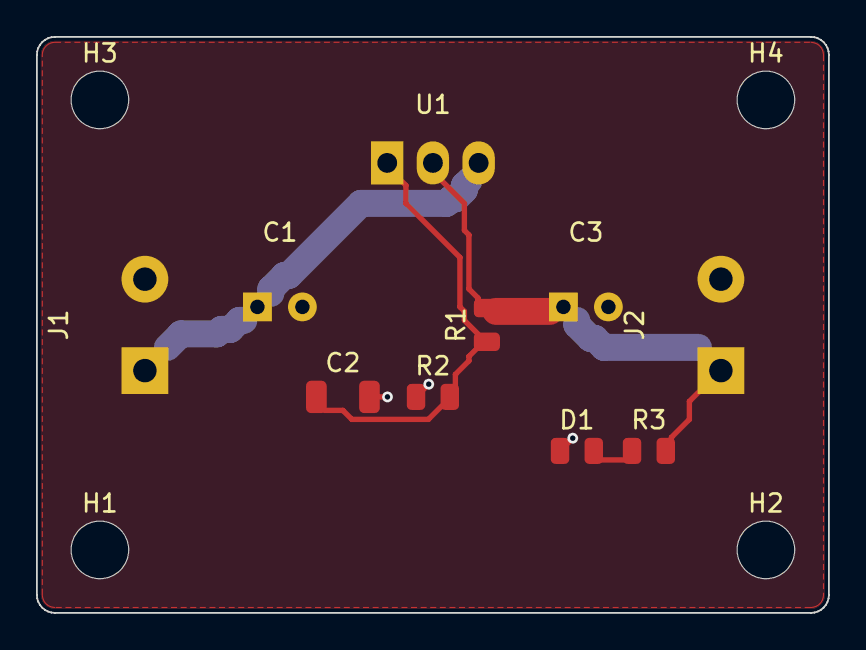
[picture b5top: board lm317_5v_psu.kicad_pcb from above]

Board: 2 copper layers, 44.0 x 32.0 mm, 14 parts (0 on the bottom side), 5 nets.

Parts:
C1: 10uF 25V; CP_Radial_D6.3mm_P2.5mm
C2: 10uF; C_1206
C3: 10uF 16V; CP_Radial_D6.3mm_P2.5mm
D1: LED green; C_0805
H1, H2, H3, H4: MountingHole_3.2mm
J1: VIN 12V; TerminalBlock_1x02_P5.08mm
J2: VOUT 5V; TerminalBlock_1x02_P5.08mm
R1: 240; C_0805
R2: 715; C_0805
R3: 1k; C_0805
U1: LM317; TO-220-3_Vertical

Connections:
ADJ: C2.1, R1.1, R2.2, U1.1
GND: C1.2, C2.2, C3.2, D1.1, J1.2, J2.2, R2.1
LED: D1.2, R3.1
VIN: C1.1, J1.1, U1.3
VOUT: C3.1, J2.1, R1.2, R3.2, U1.2

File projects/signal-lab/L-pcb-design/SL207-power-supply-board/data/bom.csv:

refs,qty,value,footprint,mpn
C1,1,10uF 25V,CP_Radial_D6.3mm_P2.5mm,
C2,1,10uF,C_1206,
C3,1,10uF 16V,CP_Radial_D6.3mm_P2.5mm,
D1,1,LED green,C_0805,
J1,1,VIN 12V,TerminalBlock_1x02_P5.08mm,
J2,1,VOUT 5V,TerminalBlock_1x02_P5.08mm,
R1,1,240,C_0805,
R2,1,715,C_0805,
R3,1,1k,C_0805,
U1,1,LM317,TO-220-3_Vertical,TO-220 adjustable regulator
